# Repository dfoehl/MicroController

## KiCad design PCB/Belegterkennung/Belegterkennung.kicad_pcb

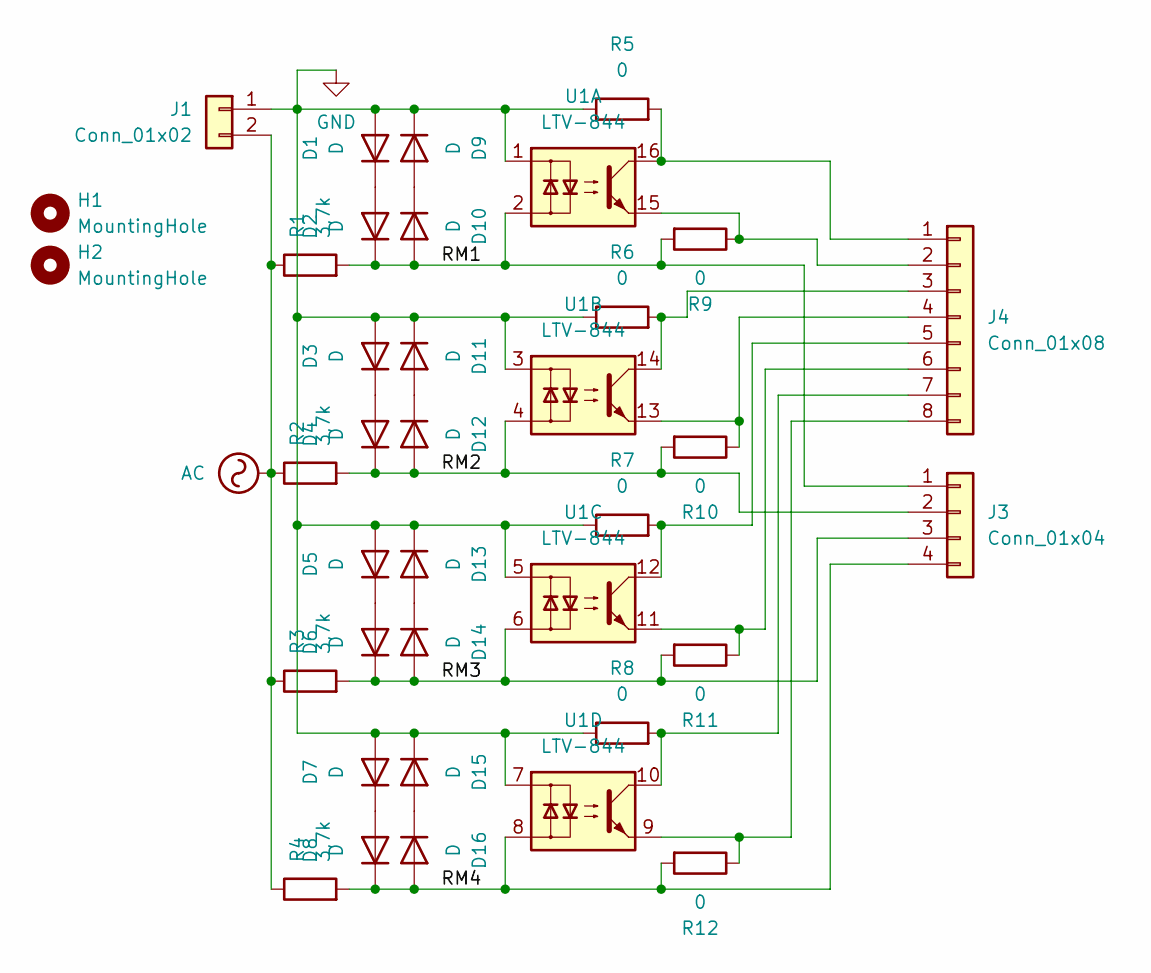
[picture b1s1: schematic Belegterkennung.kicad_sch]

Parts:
D1, D2, D3, D4, D5, D6, D7, D8, D9, D10, D11, D12, D13, D14, D15, D16: D; D_SMB
H1, H2: MountingHole; MountingHole_2.7mm_Pad
J1: Conn_01x02; TerminalBlock_RND_205-00287_1x02_P5.08mm_Horizontal
J3: Conn_01x04; TerminalBlock_RND_205-00289_1x04_P5.08mm_Horizontal
J4: Conn_01x08; TerminalBlock_RND_205-00293_1x08_P5.08mm_Horizontal
R1, R2, R3, R4: 3,7k; R_0805_2012Metric_Pad1.20x1.40mm_HandSolder
R5, R6, R7, R8, R9, R10, R11, R12: 0; R_0805_2012Metric_Pad1.20x1.40mm_HandSolder
U1: LTV-844; DIP-16_W7.62mm

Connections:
/RM1: D2.1 (K), D10.2 (A), J3.1, R1.2, R9.2, U1.2
/RM2: D4.1 (K), D12.2 (A), J3.2, R2.2, R10.2, U1.4
/RM3: D6.1 (K), D14.2 (A), J3.3, R3.2, R11.2, U1.6
/RM4: D8.1 (K), D16.2 (A), J3.4, R4.2, R12.2, U1.8
AC: J1.2, R1.1, R2.1, R3.1, R4.1
GND: D1.2 (A), D3.2 (A), D5.2 (A), D7.2 (A), D9.1 (K), D11.1 (K), D13.1 (K), D15.1 (K), J1.1, R5.1, R6.1, R7.1, R8.1, U1.1, U1.3, U1.5, U1.7
unnamed: D1.1 (K), D2.2 (A)
unnamed: D3.1 (K), D4.2 (A)
unnamed: D5.1 (K), D6.2 (A)
unnamed: D7.1 (K), D8.2 (A)
unnamed: D9.2 (A), D10.1 (K)
unnamed: D11.2 (A), D12.1 (K)
unnamed: D13.2 (A), D14.1 (K)
unnamed: D15.2 (A), D16.1 (K)
unnamed: J4.1, R5.2, U1.16
unnamed: J4.2, R9.1, U1.15
unnamed: J4.3, R6.2, U1.14
unnamed: J4.4, R10.1, U1.13
unnamed: J4.5, R7.2, U1.12
unnamed: J4.6, R11.1, U1.11
unnamed: J4.7, R8.2, U1.10
unnamed: J4.8, R12.1, U1.9

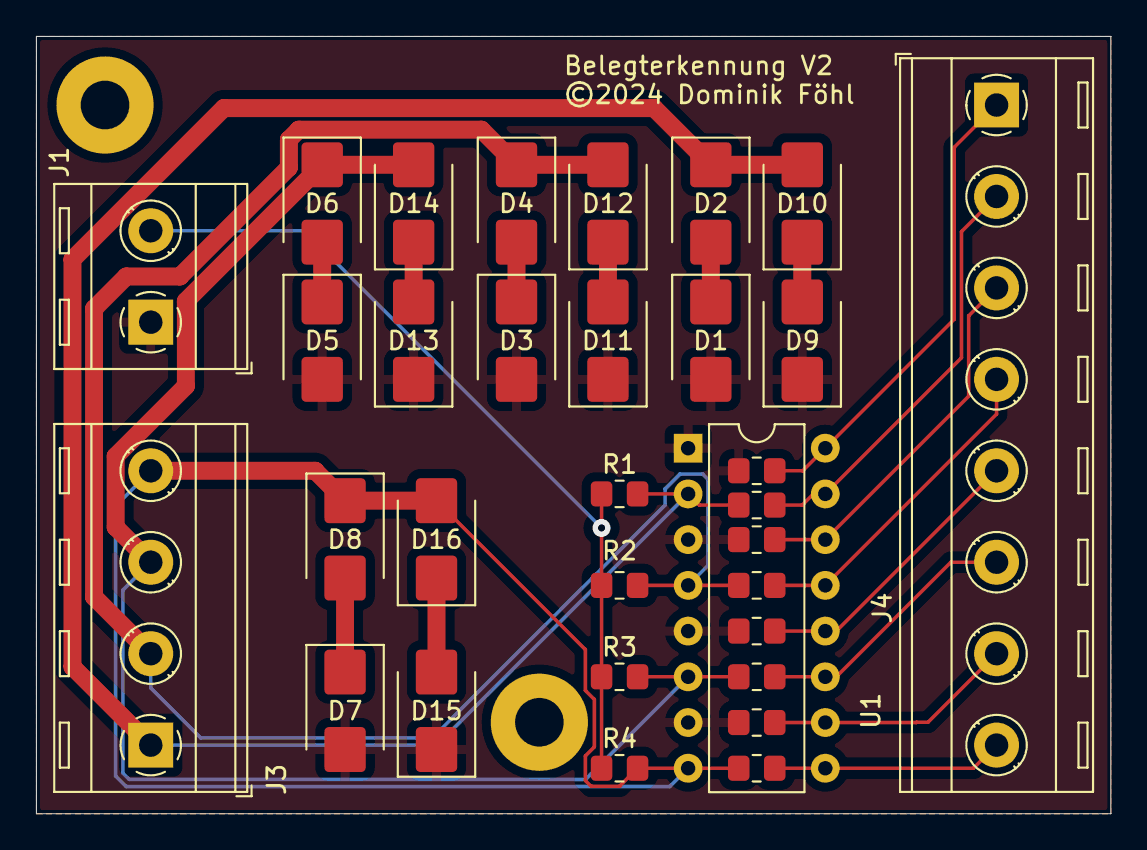
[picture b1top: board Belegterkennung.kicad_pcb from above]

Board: 2 copper layers, 59.7 x 43.2 mm, 34 parts (0 on the bottom side), 22 nets.

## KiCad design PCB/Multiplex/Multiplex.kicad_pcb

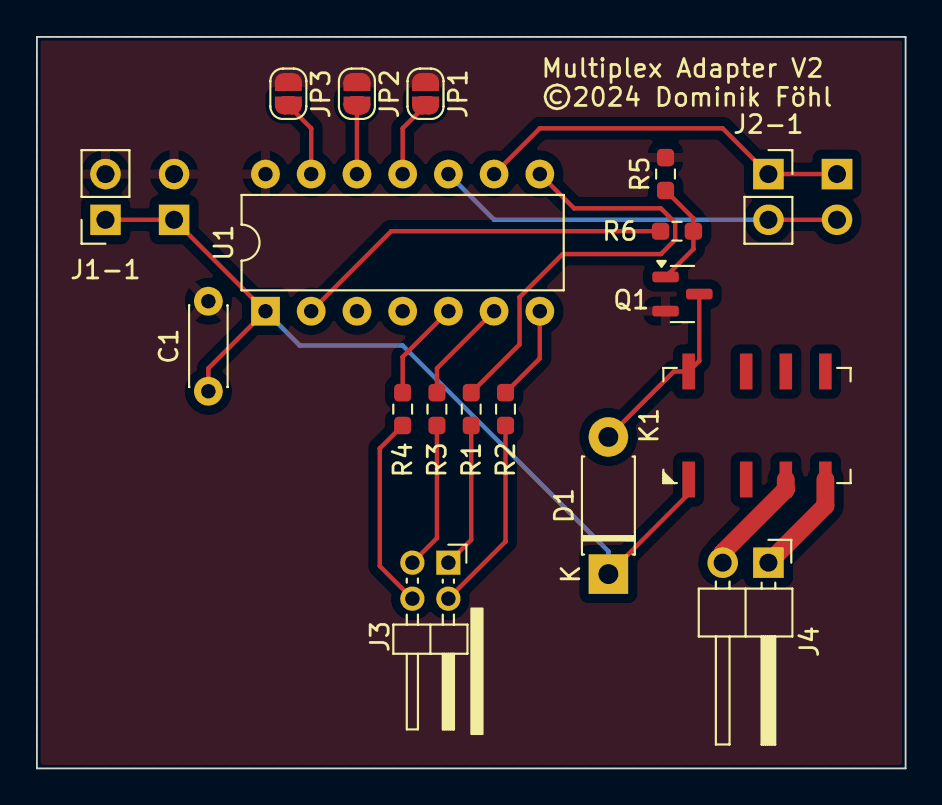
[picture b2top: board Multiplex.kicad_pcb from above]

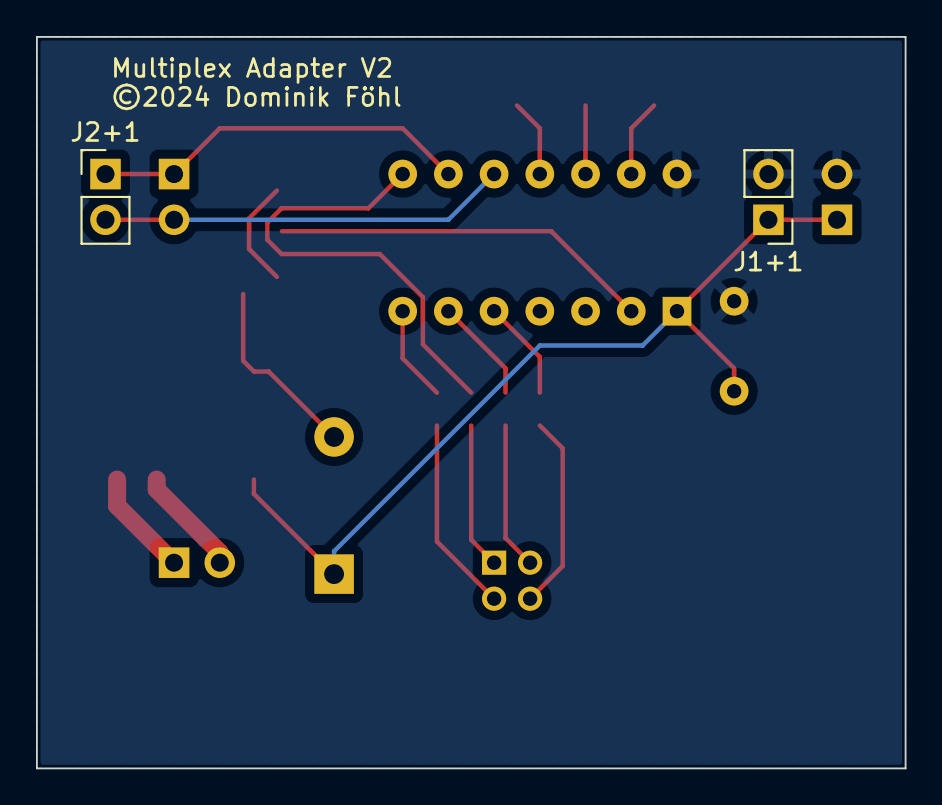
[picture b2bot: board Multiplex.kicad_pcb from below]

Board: 2 copper layers, 48.3 x 40.6 mm, 20 parts (2 on the bottom side), 20 nets.

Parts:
C1: 470n; C_Disc_D4.3mm_W1.9mm_P5.00mm
D1: 1N 4007-13; D_DO-41_SOD81_P7.62mm_Horizontal
J1+1: Power; PinHeader_1x02_P2.54mm_Vertical
J1-1: Power; PinSocket_1x02_P2.54mm_Vertical
J2+1: I2C; PinHeader_1x02_P2.54mm_Vertical
J2-1: I2C; PinSocket_1x02_P2.54mm_Vertical
J3: Signal; PinHeader_2x02_P2.00mm_Horizontal
J4: Track; PinHeader_1x02_P2.54mm_Horizontal
JP1: I2C Bit 1; SolderJumper-2_P1.3mm_Open_RoundedPad1.0x1.5mm
JP2: I2C Bit 2; SolderJumper-2_P1.3mm_Open_RoundedPad1.0x1.5mm
JP3: I2C Bit 3; SolderJumper-2_P1.3mm_Open_RoundedPad1.0x1.5mm
K1: IM03; Relay_2P2T_10x6mm_TE_IMxxG
Q1: 2N7002; SOT-23
R1, R2, R3, R4: 330; R_0603_1608Metric_Pad0.98x0.95mm_HandSolder
R5: 10k; R_0603_1608Metric_Pad0.98x0.95mm_HandSolder
R6: 0; R_0603_1608Metric_Pad0.98x0.95mm_HandSolder
U1: PIC16F1503-IP; DIP-14_W7.62mm

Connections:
+5V: C1.1, D1.1 (K), J1+1.1, J1-1.1, K1.1, U1.1 (VDD)
GND: C1.2, J1+1.2, J1-1.2, JP1.1 (A), JP2.1 (A), JP3.1 (A), Q1.2 (S), R5.2, U1.14 (VSS)
unnamed: D1.2 (A), K1.8, Q1.3 (D)
unnamed: J2+1.1, J2-1.1, U1.9 (SDI/SDA/PWM4/NCO1/C2IN1-/C1IN1-/AN5/RC1)
unnamed: J2+1.2, J2-1.2, U1.10 (SCK/SCL/CLC2/C2IN+/AN4/RC0)
unnamed: J3.1, R1.1
unnamed: J3.2, R2.1
unnamed: J3.3, R3.1
unnamed: J3.4, R4.1
unnamed: J4.1, K1.4
unnamed: J4.2, K1.3
unnamed: JP1.2 (B), U1.11 (RA2/AN2/DACOUT2/C1OUT/T0CKI/~CWG1FLT/CL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)
unnamed: JP2.2 (B), U1.12 (RA1/AN1/Vref+/C1IN0-/C2IN0-/ICSPCLK)
unnamed: JP3.2 (B), U1.13 (RA0/AN0/DACOUT1/C1IN+/ICSPDAT)
unnamed: Q1.1 (G), R5.1, R6.2
unnamed: R3.2, U1.6 (CLC2IN1/CWG1B/C2OUT/RC4)
unnamed: R4.2, U1.5 (PWM1/CLC1/CWG1A/RC5)
unnamed: R6.1, U1.2 (RA5/T1CKI/NCO1CLK/CLCIN1/CLKIN)
unnamed: R1.2, U1.8 (SDO/C2IN2-/C1IN2-/AN6/RC2)
unnamed: R2.2, U1.7 (~SS/PWM2/CLCIN0/C2IN3-/C1IN3-/AN7/RC3)

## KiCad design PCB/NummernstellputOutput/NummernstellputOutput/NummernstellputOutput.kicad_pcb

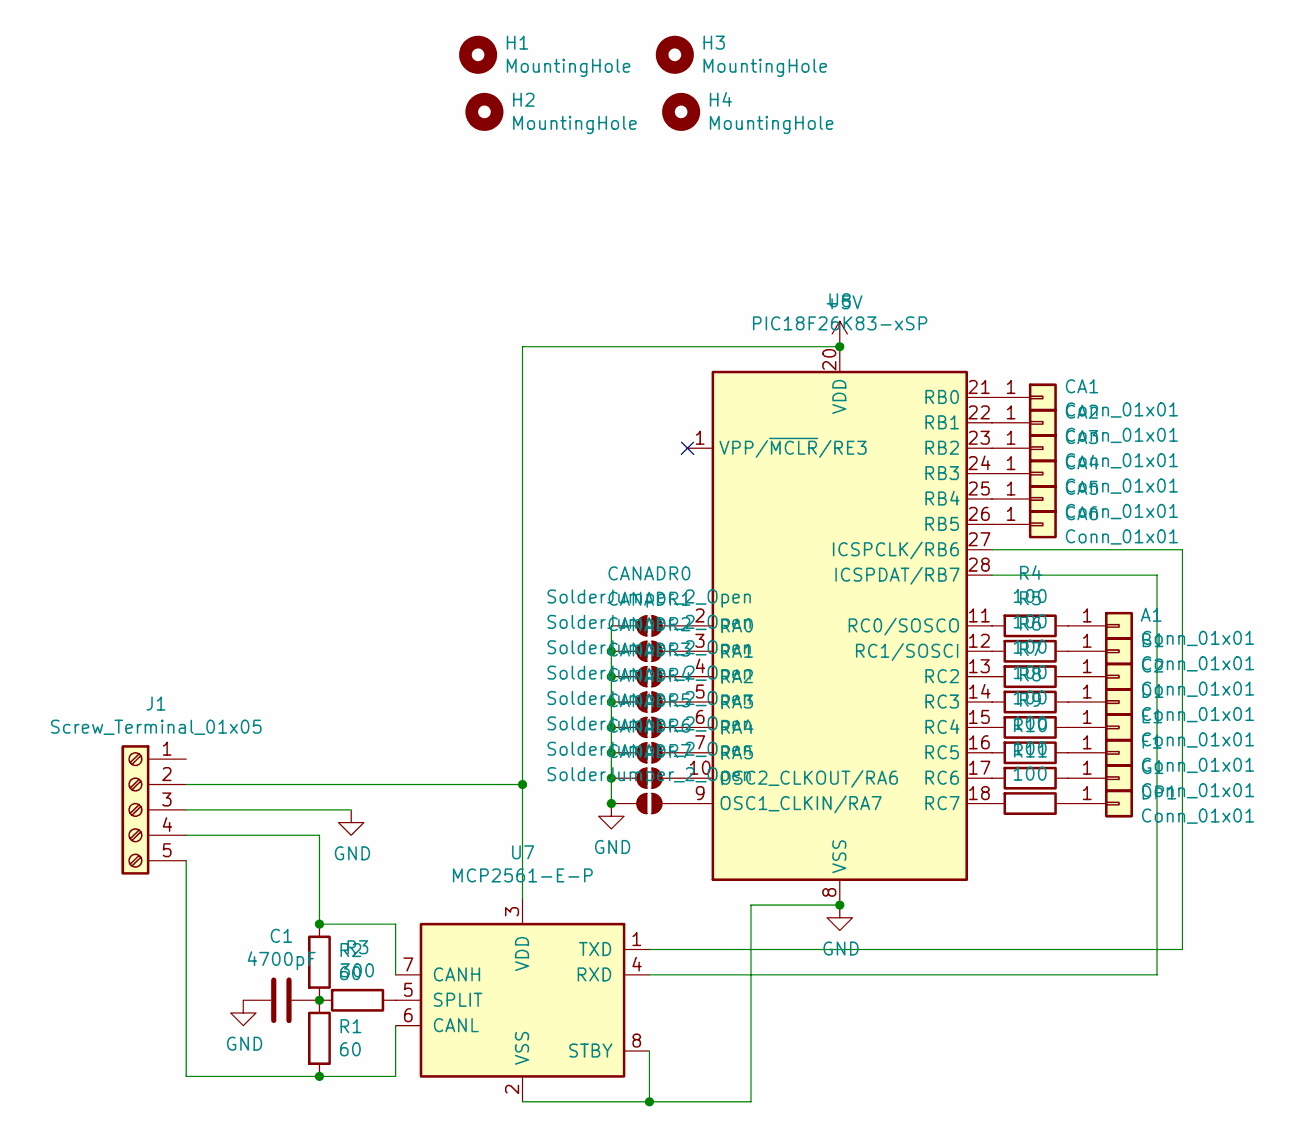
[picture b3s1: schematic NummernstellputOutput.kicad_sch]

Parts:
A1: Conn_01x01; SolderWirePad_1x01_SMD_5x10mm
B1: Conn_01x01; SolderWirePad_1x01_SMD_5x10mm
C1: 4700pF; C_Disc_D11.0mm_W5.0mm_P5.00mm
C2: Conn_01x01; SolderWirePad_1x01_SMD_5x10mm
CA1, CA2, CA3, CA4, CA5, CA6: Conn_01x01; SolderWirePad_1x01_SMD_5x10mm
CANADR0, CANADR1, CANADR2, CANADR3, CANADR4, CANADR5, CANADR6, CANADR7: SolderJumper_2_Open; SolderJumper-2_P1.3mm_Open_RoundedPad1.0x1.5mm
D1: Conn_01x01; SolderWirePad_1x01_SMD_5x10mm
DP1: Conn_01x01; SolderWirePad_1x01_SMD_5x10mm
E1: Conn_01x01; SolderWirePad_1x01_SMD_5x10mm
F1: Conn_01x01; SolderWirePad_1x01_SMD_5x10mm
G1: Conn_01x01; SolderWirePad_1x01_SMD_5x10mm
H1, H2, H3, H4: MountingHole; MountingHole_3.5mm_Pad
J1: Screw_Terminal_01x05; TerminalBlock_RND_205-00235_1x05_P5.08mm_Horizontal
R1, R2: 60; R_Axial_DIN0207_L6.3mm_D2.5mm_P10.16mm_Horizontal
R3: 300; R_Axial_DIN0207_L6.3mm_D2.5mm_P10.16mm_Horizontal
R4, R5, R6, R7, R8, R9, R10, R11: 100; R_Axial_DIN0207_L6.3mm_D2.5mm_P10.16mm_Horizontal
U7: MCP2561-E-P; DIP-8_W7.62mm
U8: PIC18F26K83-xSP; DIP-28_W7.62mm

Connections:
+5V: J1.2, U7.3 (VDD), U8.20 (VDD)
GND: C1.2, CANADR0.1 (A), CANADR1.1 (A), CANADR2.1 (A), CANADR3.1 (A), CANADR4.1 (A), CANADR5.1 (A), CANADR6.1 (A), CANADR7.1 (A), J1.3, U7.2 (VSS), U7.8 (STBY), U8.8 (VSS), U8.19 (VSS)
unnamed: A1.1, R4.1
unnamed: B1.1, R5.1
unnamed: C1.1, R1.1, R2.2, R3.2
unnamed: C2.1, R6.1
unnamed: CA1.1, U8.21 (RB0)
unnamed: CA2.1, U8.22 (RB1)
unnamed: CA3.1, U8.23 (RB2)
unnamed: CA4.1, U8.24 (RB3)
unnamed: CA5.1, U8.25 (RB4)
unnamed: CA6.1, U8.26 (RB5)
unnamed: CANADR0.2 (B), U8.2 (RA0)
unnamed: CANADR1.2 (B), U8.3 (RA1)
unnamed: CANADR2.2 (B), U8.4 (RA2)
unnamed: CANADR3.2 (B), U8.5 (RA3)
unnamed: CANADR4.2 (B), U8.6 (RA4)
unnamed: CANADR5.2 (B), U8.7 (RA5)
unnamed: CANADR6.2 (B), U8.10 (OSC2_CLKOUT/RA6)
unnamed: CANADR7.2 (B), U8.9 (OSC1_CLKIN/RA7)
unnamed: D1.1, R7.1
unnamed: DP1.1, R11.1
unnamed: E1.1, R8.1
unnamed: F1.1, R9.1
unnamed: G1.1, R10.1
unnamed: J1.4, R2.1, U7.7 (CANH)
unnamed: J1.5, R1.2, U7.6 (CANL)
unnamed: U7.4 (RXD), U8.28 (ICSPDAT/RB7)
unnamed: R3.1, U7.5 (SPLIT)
unnamed: U7.1 (TXD), U8.27 (ICSPCLK/RB6)
unnamed: R4.2, U8.11 (RC0/SOSCO)
unnamed: R5.2, U8.12 (RC1/SOSCI)
unnamed: R6.2, U8.13 (RC2)
unnamed: R7.2, U8.14 (RC3)
unnamed: R8.2, U8.15 (RC4)
unnamed: R9.2, U8.16 (RC5)
unnamed: R10.2, U8.17 (RC6)
unnamed: R11.2, U8.18 (RC7)

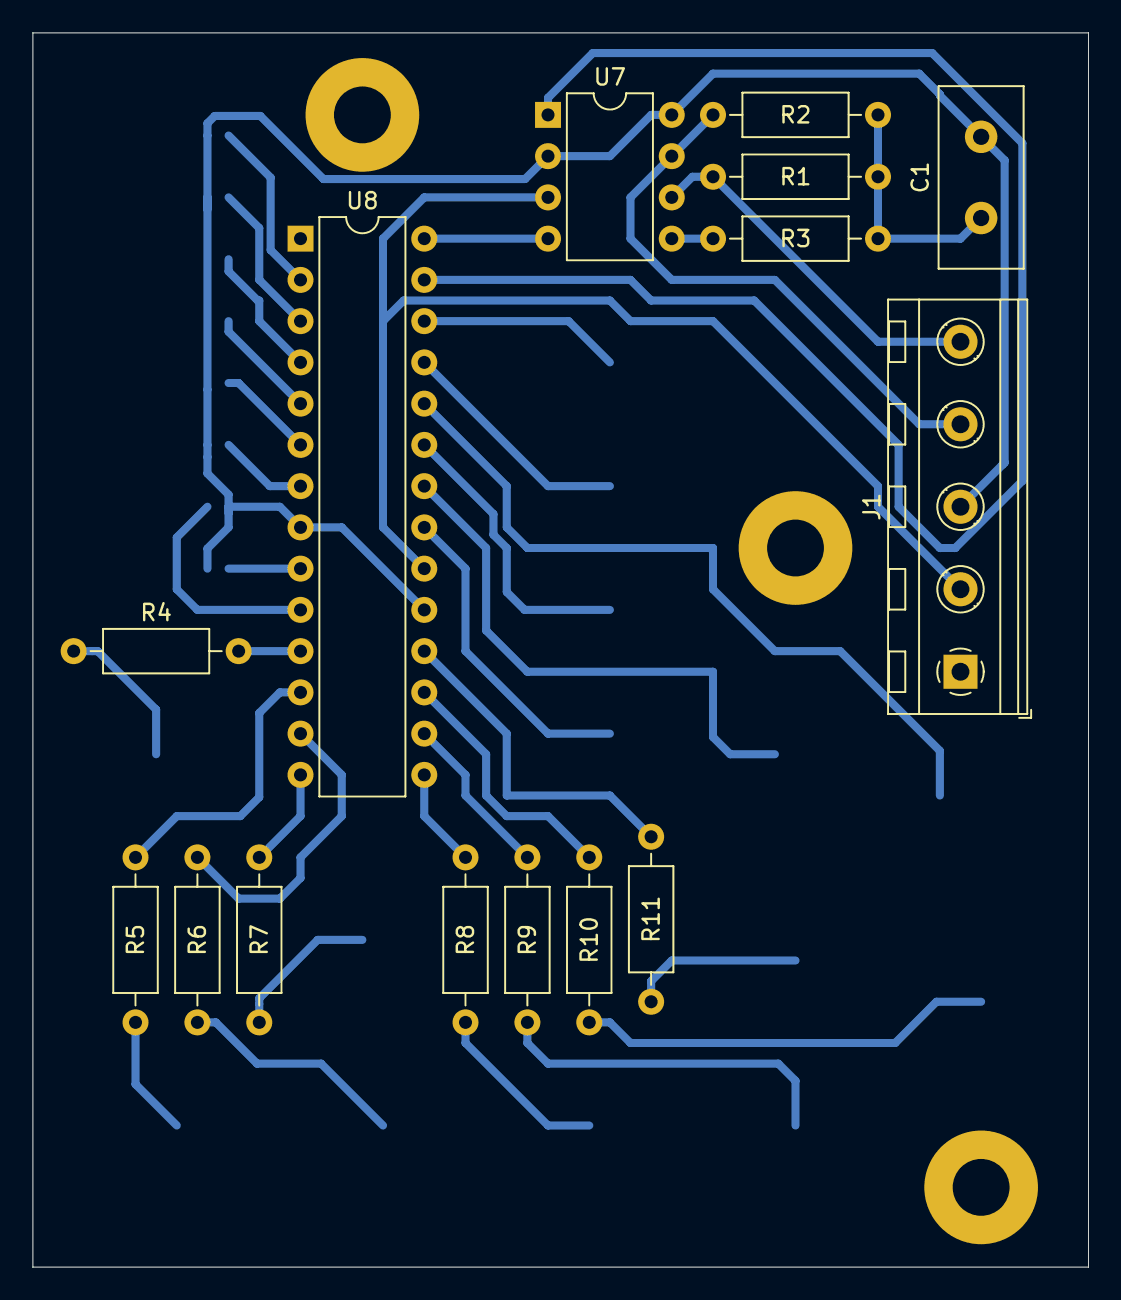
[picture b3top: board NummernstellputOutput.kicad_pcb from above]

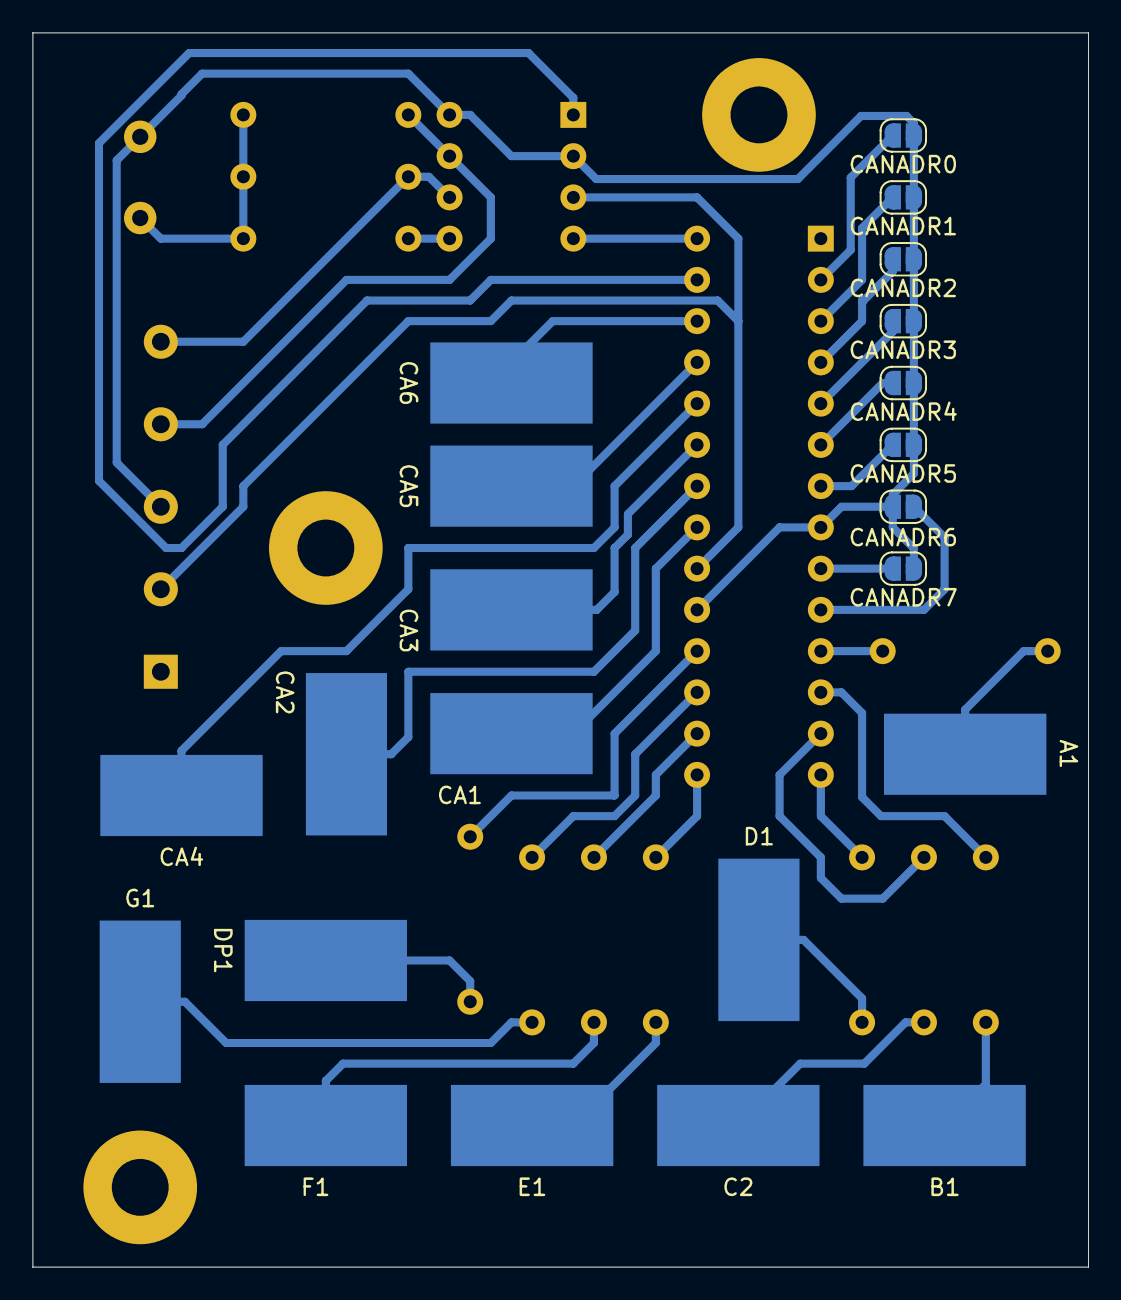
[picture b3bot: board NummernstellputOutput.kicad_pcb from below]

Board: 2 copper layers, 65.0 x 76.0 mm, 40 parts (22 on the bottom side), 38 nets.

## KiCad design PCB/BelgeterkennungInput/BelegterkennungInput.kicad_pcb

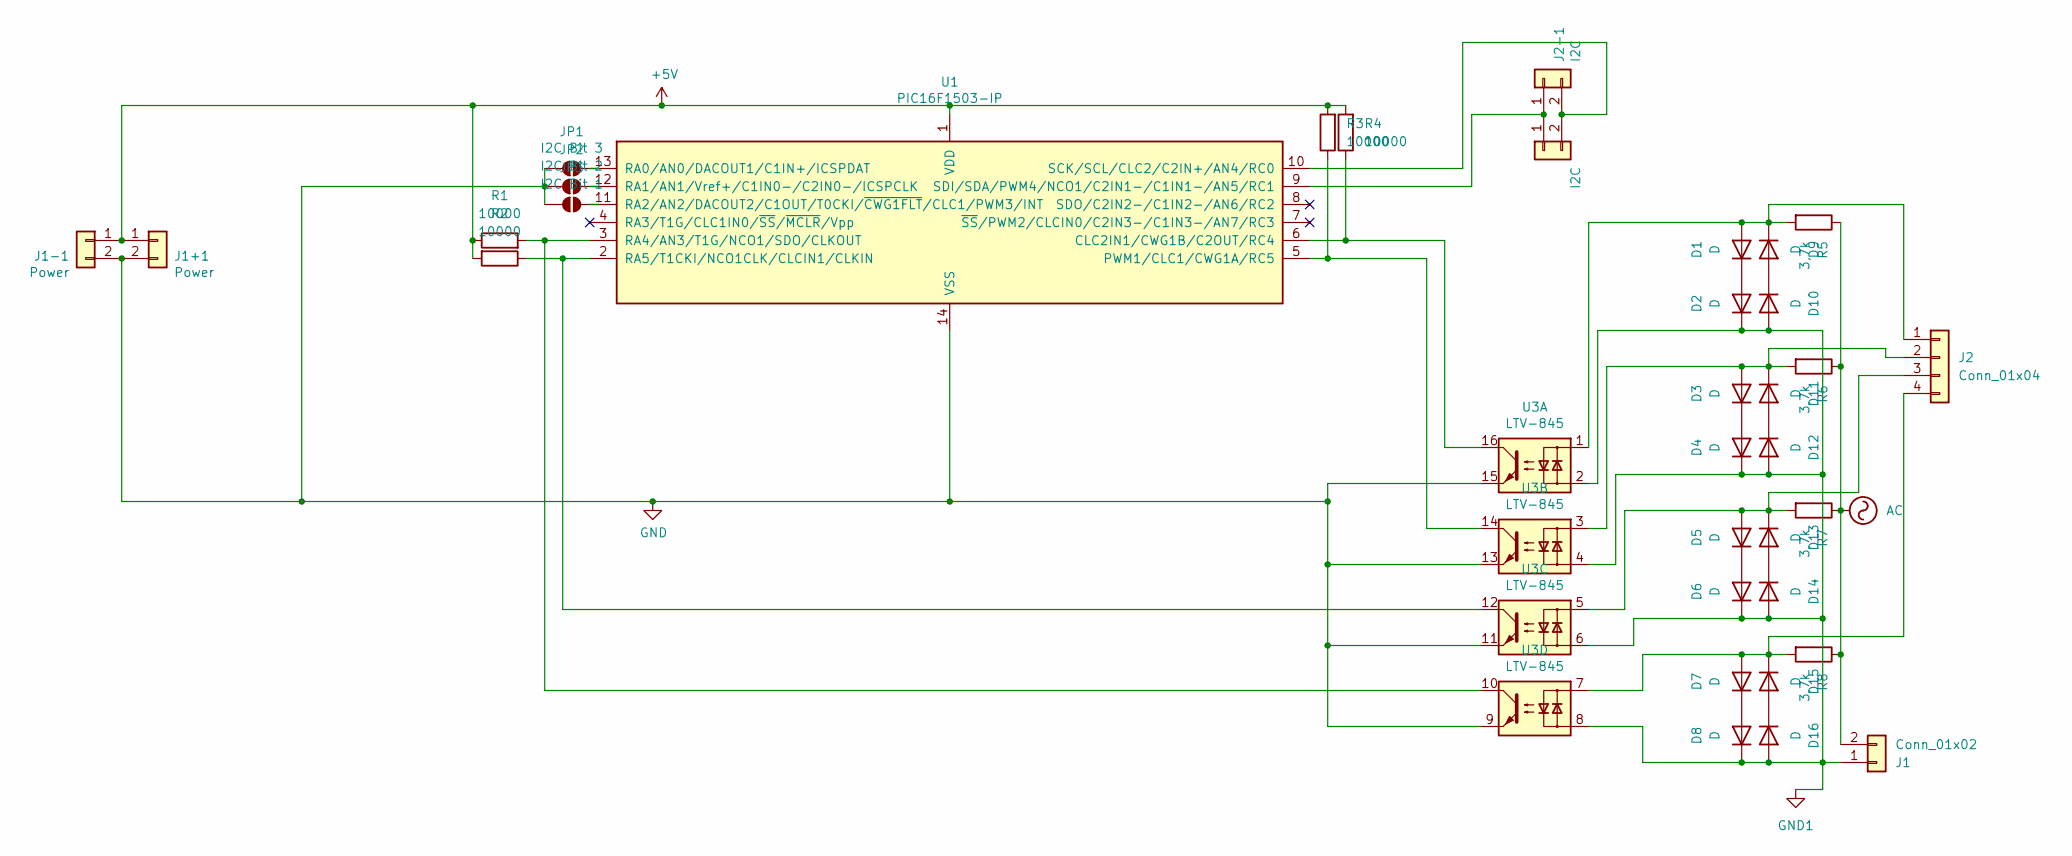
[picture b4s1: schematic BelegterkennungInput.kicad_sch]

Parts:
D1, D2, D3, D4, D5, D6, D7, D8, D9, D10, D11, D12, D13, D14, D15, D16: D; D_SMB
J1: Conn_01x02; TerminalBlock_RND_205-00287_1x02_P5.08mm_Horizontal
J1+1: Power; PinHeader_1x02_P2.54mm_Vertical
J1-1: Power; PinSocket_1x02_P2.54mm_Vertical
J2: Conn_01x04; TerminalBlock_RND_205-00289_1x04_P5.08mm_Horizontal
J2+1: I2C; PinHeader_1x02_P2.54mm_Vertical
J2-1: I2C; PinSocket_1x02_P2.54mm_Vertical
JP1: I2C Bit 3; SolderJumper-2_P1.3mm_Open_RoundedPad1.0x1.5mm
JP2: I2C Bit 2; SolderJumper-2_P1.3mm_Open_RoundedPad1.0x1.5mm
JP3: I2C Bit 1; SolderJumper-2_P1.3mm_Open_RoundedPad1.0x1.5mm
R1, R2, R3, R4: 10000; R_0603_1608Metric_Pad0.98x0.95mm_HandSolder
R5, R6, R7, R8: 3,7k; R_0805_2012Metric_Pad1.20x1.40mm_HandSolder
U1: PIC16F1503-IP; DIP-14_W7.62mm
U3: LTV-845; DIP-16_W7.62mm

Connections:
+5V: J1+1.1, J1-1.1, R1.1, R2.2, R3.2, R4.2, U1.1 (VDD)
AC: J1.2, R5.1, R6.1, R7.1, R8.1
GND: J1+1.2, J1-1.2, JP1.1 (A), JP2.1 (A), JP3.1 (A), U1.14 (VSS); also elsewhere on the board
GND1: D2.1 (K), D4.1 (K), D6.1 (K), D8.1 (K), D10.2 (A), D12.2 (A), D14.2 (A), D16.2 (A), J1.1; also elsewhere on the board
unnamed 4: D1.2 (A), D9.1 (K), J2.1, R5.2; also elsewhere on the board
unnamed: D1.1 (K), D2.2 (A)
unnamed: D3.1 (K), D4.2 (A)
unnamed: D5.1 (K), D6.2 (A)
unnamed: D7.1 (K), D8.2 (A)
unnamed: D9.2 (A), D10.1 (K)
unnamed: D11.2 (A), D12.1 (K)
unnamed 11: D3.2 (A), D11.1 (K), J2.2, R6.2; also elsewhere on the board
unnamed: D13.2 (A), D14.1 (K)
unnamed 13: D5.2 (A), D13.1 (K), J2.3, R7.2; also elsewhere on the board
unnamed: D15.2 (A), D16.1 (K)
unnamed 15: D7.2 (A), D15.1 (K), J2.4, R8.2; also elsewhere on the board
unnamed: J2+1.1, J2-1.1, U1.9 (SDI/SDA/PWM4/NCO1/C2IN1-/C1IN1-/AN5/RC1)
unnamed: J2+1.2, J2-1.2, U1.10 (SCK/SCL/CLC2/C2IN+/AN4/RC0)
unnamed: JP1.2 (B), U1.13 (RA0/AN0/DACOUT1/C1IN+/ICSPDAT)
unnamed: JP2.2 (B), U1.12 (RA1/AN1/Vref+/C1IN0-/C2IN0-/ICSPCLK)
unnamed: JP3.2 (B), U1.11 (RA2/AN2/DACOUT2/C1OUT/T0CKI/~CWG1FLT/CL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)
unnamed 21: R4.1, U1.6 (CLC2IN1/CWG1B/C2OUT/RC4); also elsewhere on the board
unnamed 22: R3.1, U1.5 (PWM1/CLC1/CWG1A/RC5); also elsewhere on the board
unnamed 23: R1.2, U1.3 (RA4/AN3/T1G/NCO1/SDO/CLKOUT); also elsewhere on the board
unnamed 24: R2.1, U1.2 (RA5/T1CKI/NCO1CLK/CLCIN1/CLKIN); also elsewhere on the board

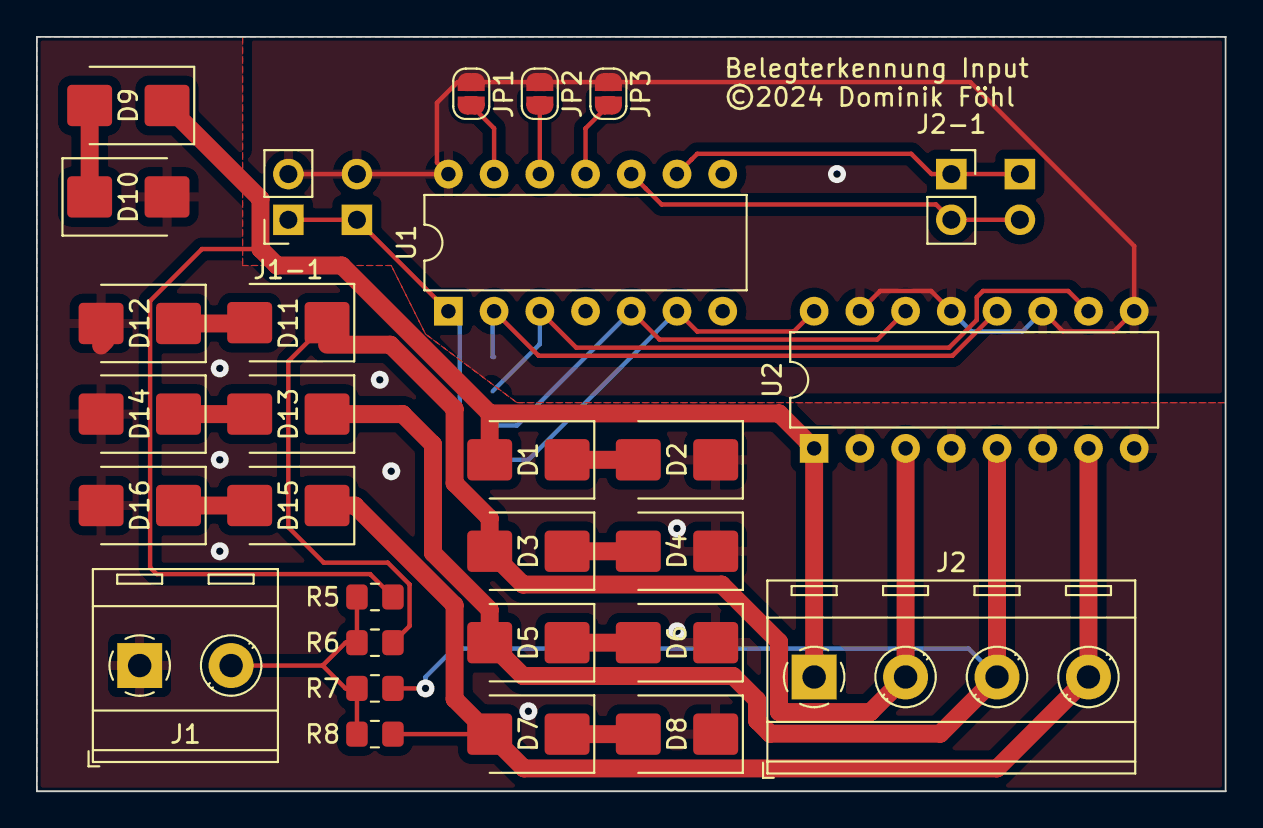
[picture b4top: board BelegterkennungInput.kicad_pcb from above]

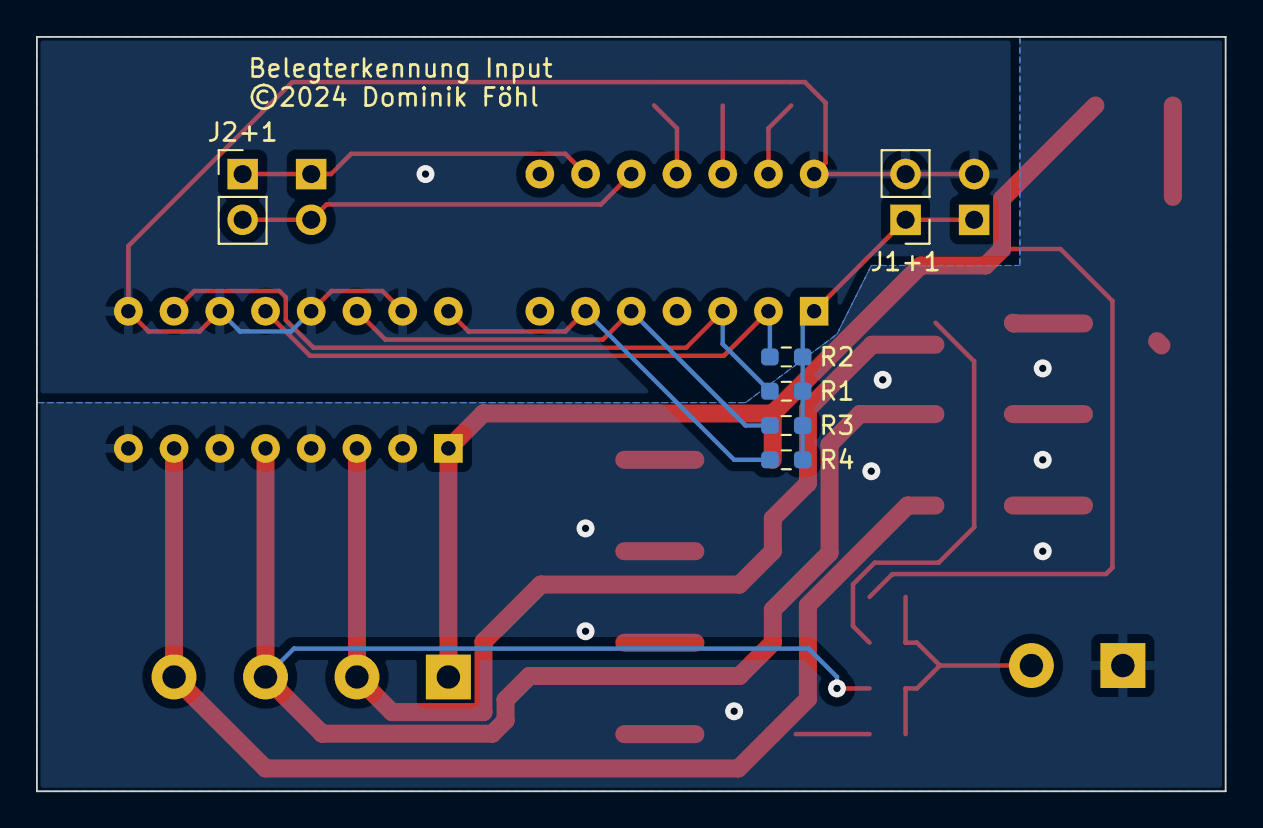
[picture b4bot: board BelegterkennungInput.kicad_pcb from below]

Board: 2 copper layers, 66.0 x 41.9 mm, 35 parts (6 on the bottom side), 25 nets.

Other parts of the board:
U2: LTV-845; DIP-16_W7.62mm

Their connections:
GND: U2.9, U2.11, U2.13, U2.15; also elsewhere on the board
GND1: U2.2, U2.4, U2.6, U2.8; also elsewhere on the board
unnamed 4: U2.1; also elsewhere on the board
unnamed 11: U2.3; also elsewhere on the board
unnamed 13: U2.5; also elsewhere on the board
unnamed 15: U2.7; also elsewhere on the board
unnamed 21: U2.16; also elsewhere on the board
unnamed 22: U2.14; also elsewhere on the board
unnamed 23: U2.10; also elsewhere on the board
unnamed 24: U2.12; also elsewhere on the board

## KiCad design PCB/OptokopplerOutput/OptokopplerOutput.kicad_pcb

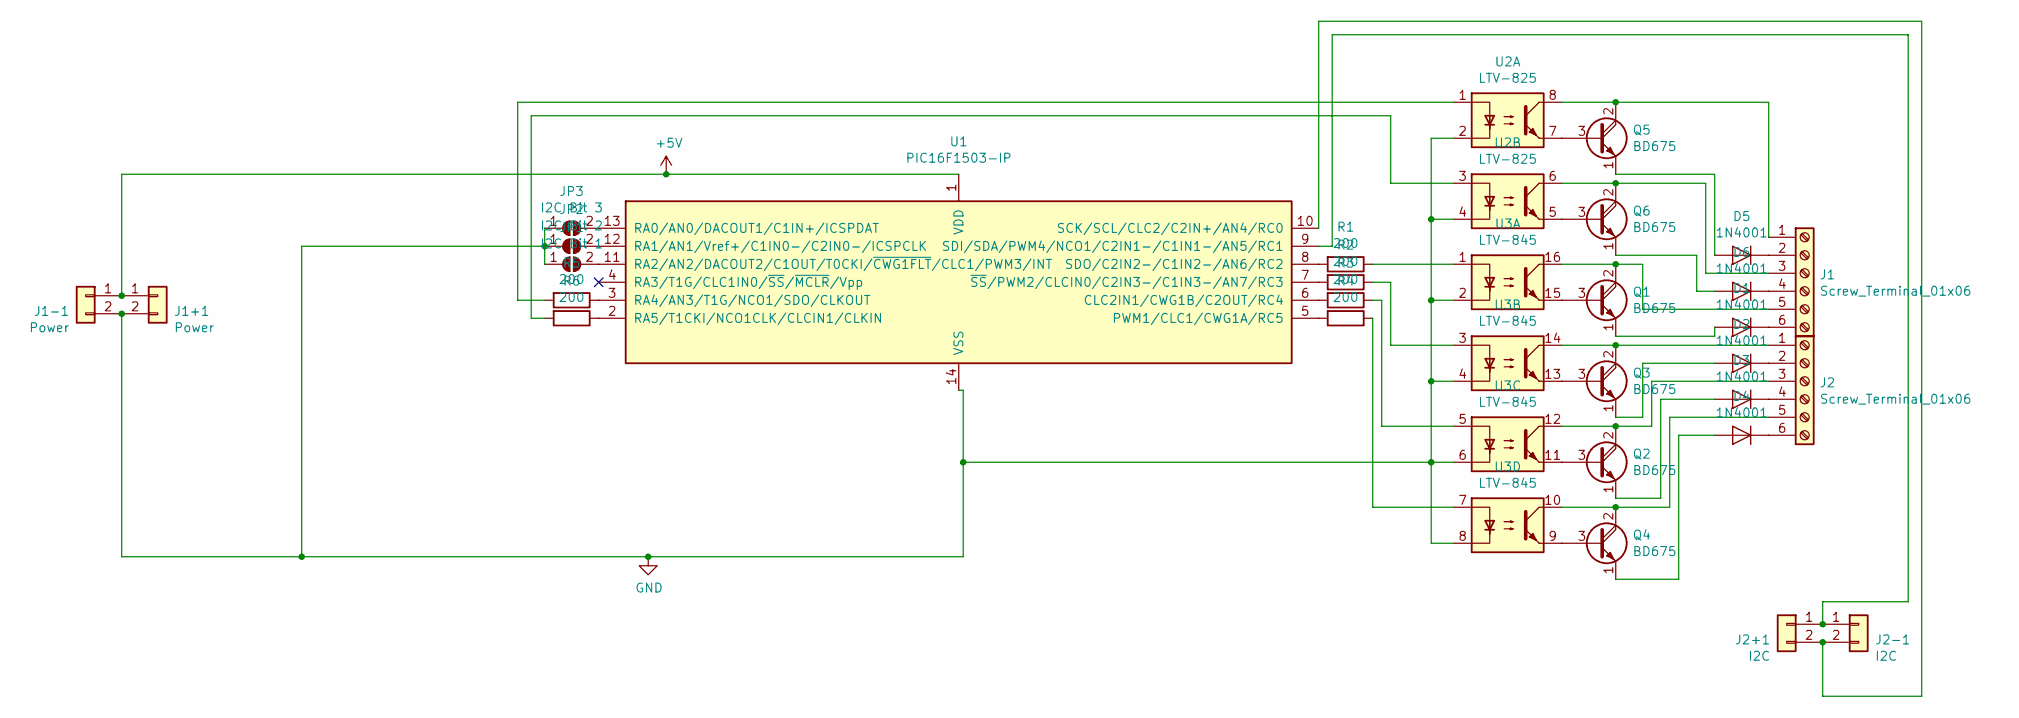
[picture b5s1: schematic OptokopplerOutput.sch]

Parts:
D1, D2, D3, D4, D5, D6: 1N4001; D_SMB_Handsoldering
J1, J2: Screw_Terminal_01x06; TerminalBlock_RND_205-00236_1x06_P5.08mm_Horizontal
J1+1: Power; PinHeader_1x02_P2.54mm_Vertical
J1-1: Power; PinSocket_1x02_P2.54mm_Vertical
J2+1: I2C; PinHeader_1x02_P2.54mm_Vertical
J2-1: I2C; PinSocket_1x02_P2.54mm_Vertical
JP1: I2C Bit 1; SolderJumper-2_P1.3mm_Open_RoundedPad1.0x1.5mm
JP2: I2C Bit 2; SolderJumper-2_P1.3mm_Open_RoundedPad1.0x1.5mm
JP3: I2C Bit 3; SolderJumper-2_P1.3mm_Open_RoundedPad1.0x1.5mm
Q1, Q2, Q3, Q4, Q5, Q6: BD675; TO-126-3_Vertical
R1, R2, R3, R4, R5, R6: 200; R_0603_1608Metric_Pad1.05x0.95mm_HandSolder
U1: PIC16F1503-IP; DIP-14_W7.62mm
U2: LTV-825; DIP-8_W7.62mm
U3: LTV-845; DIP-16_W7.62mm

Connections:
+5V: J1+1.1, J1-1.1, U1.1 (VDD)
GND: J1+1.2, J1-1.2, JP1.1 (A), JP2.1 (A), JP3.1 (A), U1.14 (VSS), U2.2, U2.4, U3.2, U3.4, U3.6, U3.8
unnamed: D1.1 (K), J1.6
unnamed: D1.2 (A), Q1.1 (E)
unnamed: D2.1 (K), J2.2
unnamed: D2.2 (A), Q3.1 (E)
unnamed: D3.1 (K), J2.4
unnamed: D3.2 (A), Q2.1 (E)
unnamed: D4.1 (K), J2.6
unnamed: D4.2 (A), Q4.1 (E)
unnamed: D5.1 (K), J1.2
unnamed: D5.2 (A), Q5.1 (E)
unnamed: D6.1 (K), J1.4
unnamed: D6.2 (A), Q6.1 (E)
unnamed: J1.1, Q5.2 (C), U2.8
unnamed: J1.3, Q6.2 (C), U2.6
unnamed: J1.5, Q1.2 (C), U3.16
unnamed: J2+1.1, J2-1.1, U1.9 (SDI/SDA/PWM4/NCO1/C2IN1-/C1IN1-/AN5/RC1)
unnamed: J2+1.2, J2-1.2, U1.10 (SCK/SCL/CLC2/C2IN+/AN4/RC0)
unnamed: J2.1, Q3.2 (C), U3.14
unnamed: J2.3, Q2.2 (C), U3.12
unnamed: J2.5, Q4.2 (C), U3.10
unnamed: JP1.2 (B), U1.11 (RA2/AN2/DACOUT2/C1OUT/T0CKI/~CWG1FLT~/C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)
unnamed: JP2.2 (B), U1.12 (RA1/AN1/Vref+/C1IN0-/C2IN0-/ICSPCLK)
unnamed: JP3.2 (B), U1.13 (RA0/AN0/DACOUT1/C1IN+/ICSPDAT)
unnamed: Q1.3 (B), U3.15
unnamed: Q2.3 (B), U3.11
unnamed: Q3.3 (B), U3.13
unnamed: Q4.3 (B), U3.9
unnamed: Q5.3 (B), U2.7
unnamed: Q6.3 (B), U2.5
unnamed: R1.1, U3.1
unnamed: R1.2, U1.8 (SDO/C2IN2-/C1IN2-/AN6/RC2)
unnamed: R2.1, U3.3
unnamed: R2.2, U1.7 (~SS~/PWM2/CLCIN0/C2IN3-/C1IN3-/AN7/RC3)
unnamed: R3.1, U3.5
unnamed: R3.2, U1.6 (CLC2IN1/CWG1B/C2OUT/RC4)
unnamed: R4.1, U3.7
unnamed: R4.2, U1.5 (PWM1/CLC1/CWG1A/RC5)
unnamed: R5.1, U1.3 (RA4/AN3/T1G/NCO1/SDO/CLKOUT)
unnamed: R5.2, U2.1
unnamed: R6.1, U1.2 (RA5/T1CKI/NCO1CLK/CLCIN1/CLKIN)
unnamed: R6.2, U2.3

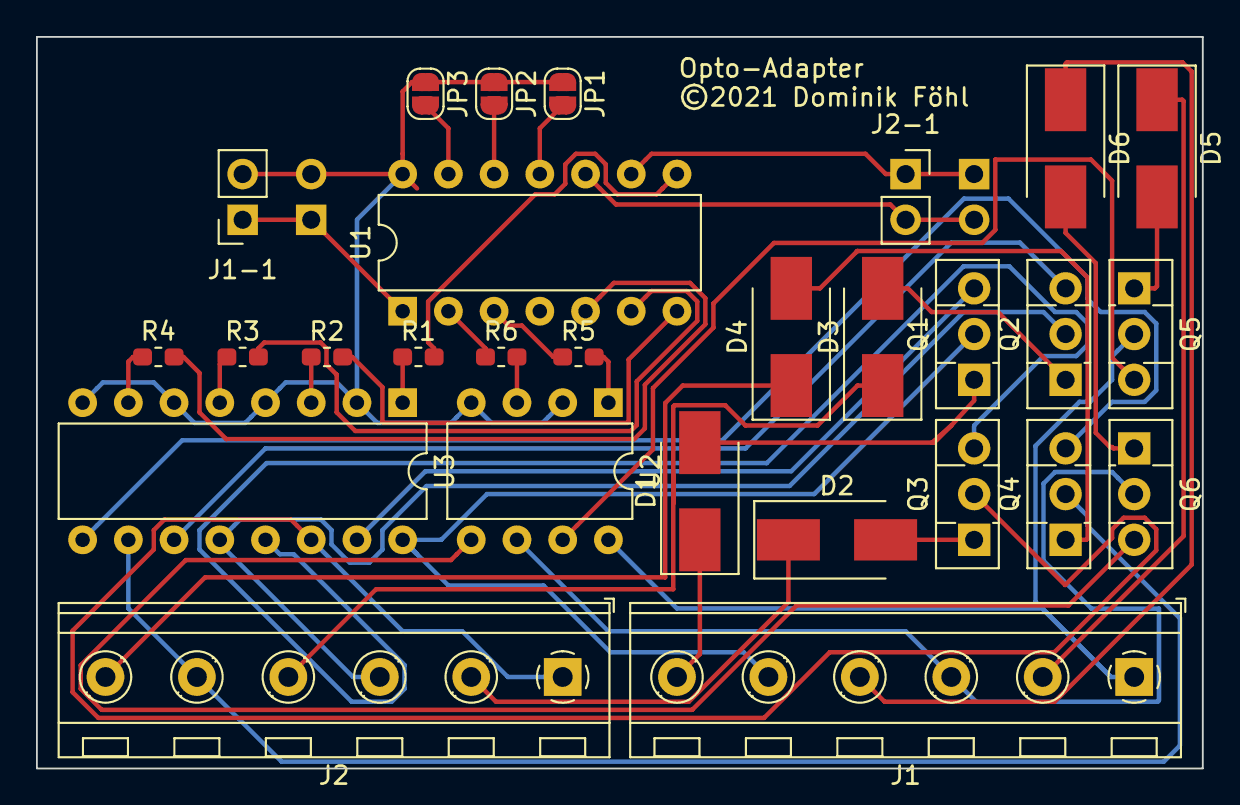
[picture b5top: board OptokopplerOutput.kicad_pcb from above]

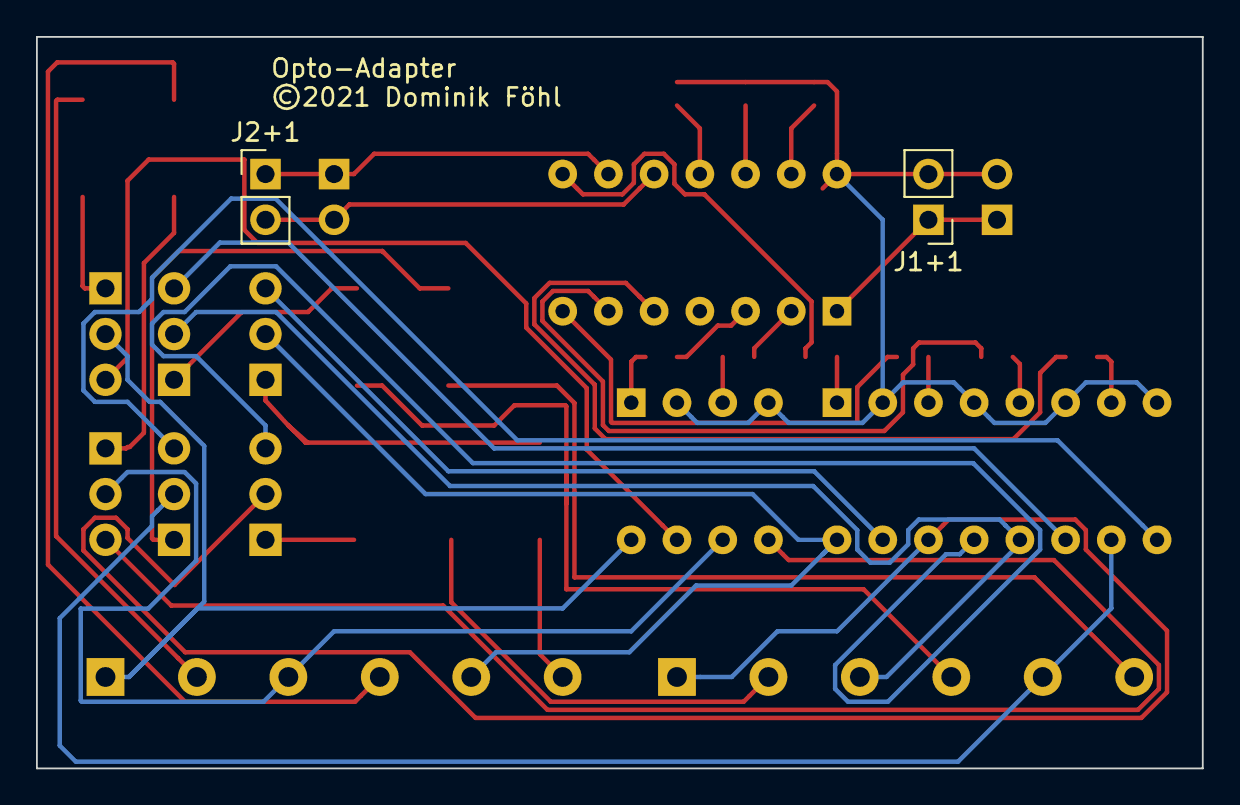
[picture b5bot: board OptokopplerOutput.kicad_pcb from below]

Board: 2 copper layers, 64.8 x 40.6 mm, 30 parts (2 on the bottom side), 43 nets.

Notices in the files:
PCB/Belegterkennung/Belegterkennung.kicad_pcb:
©2024 Dominik Föhl
PCB/I2CMaster/I2CMaster.kicad_pcb:
©2021 Dominik Föhl
PCB/OptokopplerInput/OptokopplerInput.kicad_pcb:
©2023 Dominik Föhl
